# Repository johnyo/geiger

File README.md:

geiger
======

Low Voltage 2.5V PIN Diode Based Geiger Counter

Purpose
======

Super low voltgae Geiger Counter using a modified PIN photodiode. See Bernd Laquai's paper on the subject here: http://www.opengeiger.de/ABGDetektor_en.pdf. The first stage charge amplifier gain is set by the feedback Cap and Resistor. Bigger resistor = more gain, but it pulls the output low and reduces the amplifier's swing on the negative side. 1M is about the biggest resistor you can safely use. The second stage amp takes the negative pulse from the 1st stage and inverts it and boost it x10 so it can be easily read.

Project Structure
=================

/GeigerCounter
* The Eagle PCB project

/Library
* Any components that are not found in the Eagle or SparkFun default libraries, I have made myself and they are here.

/GeigerCounter/FabricationOutput
* This holds the fabrication output script. Based on SparkFun's script. It also holds the zip file Gerber files that were sent out for fabrication.

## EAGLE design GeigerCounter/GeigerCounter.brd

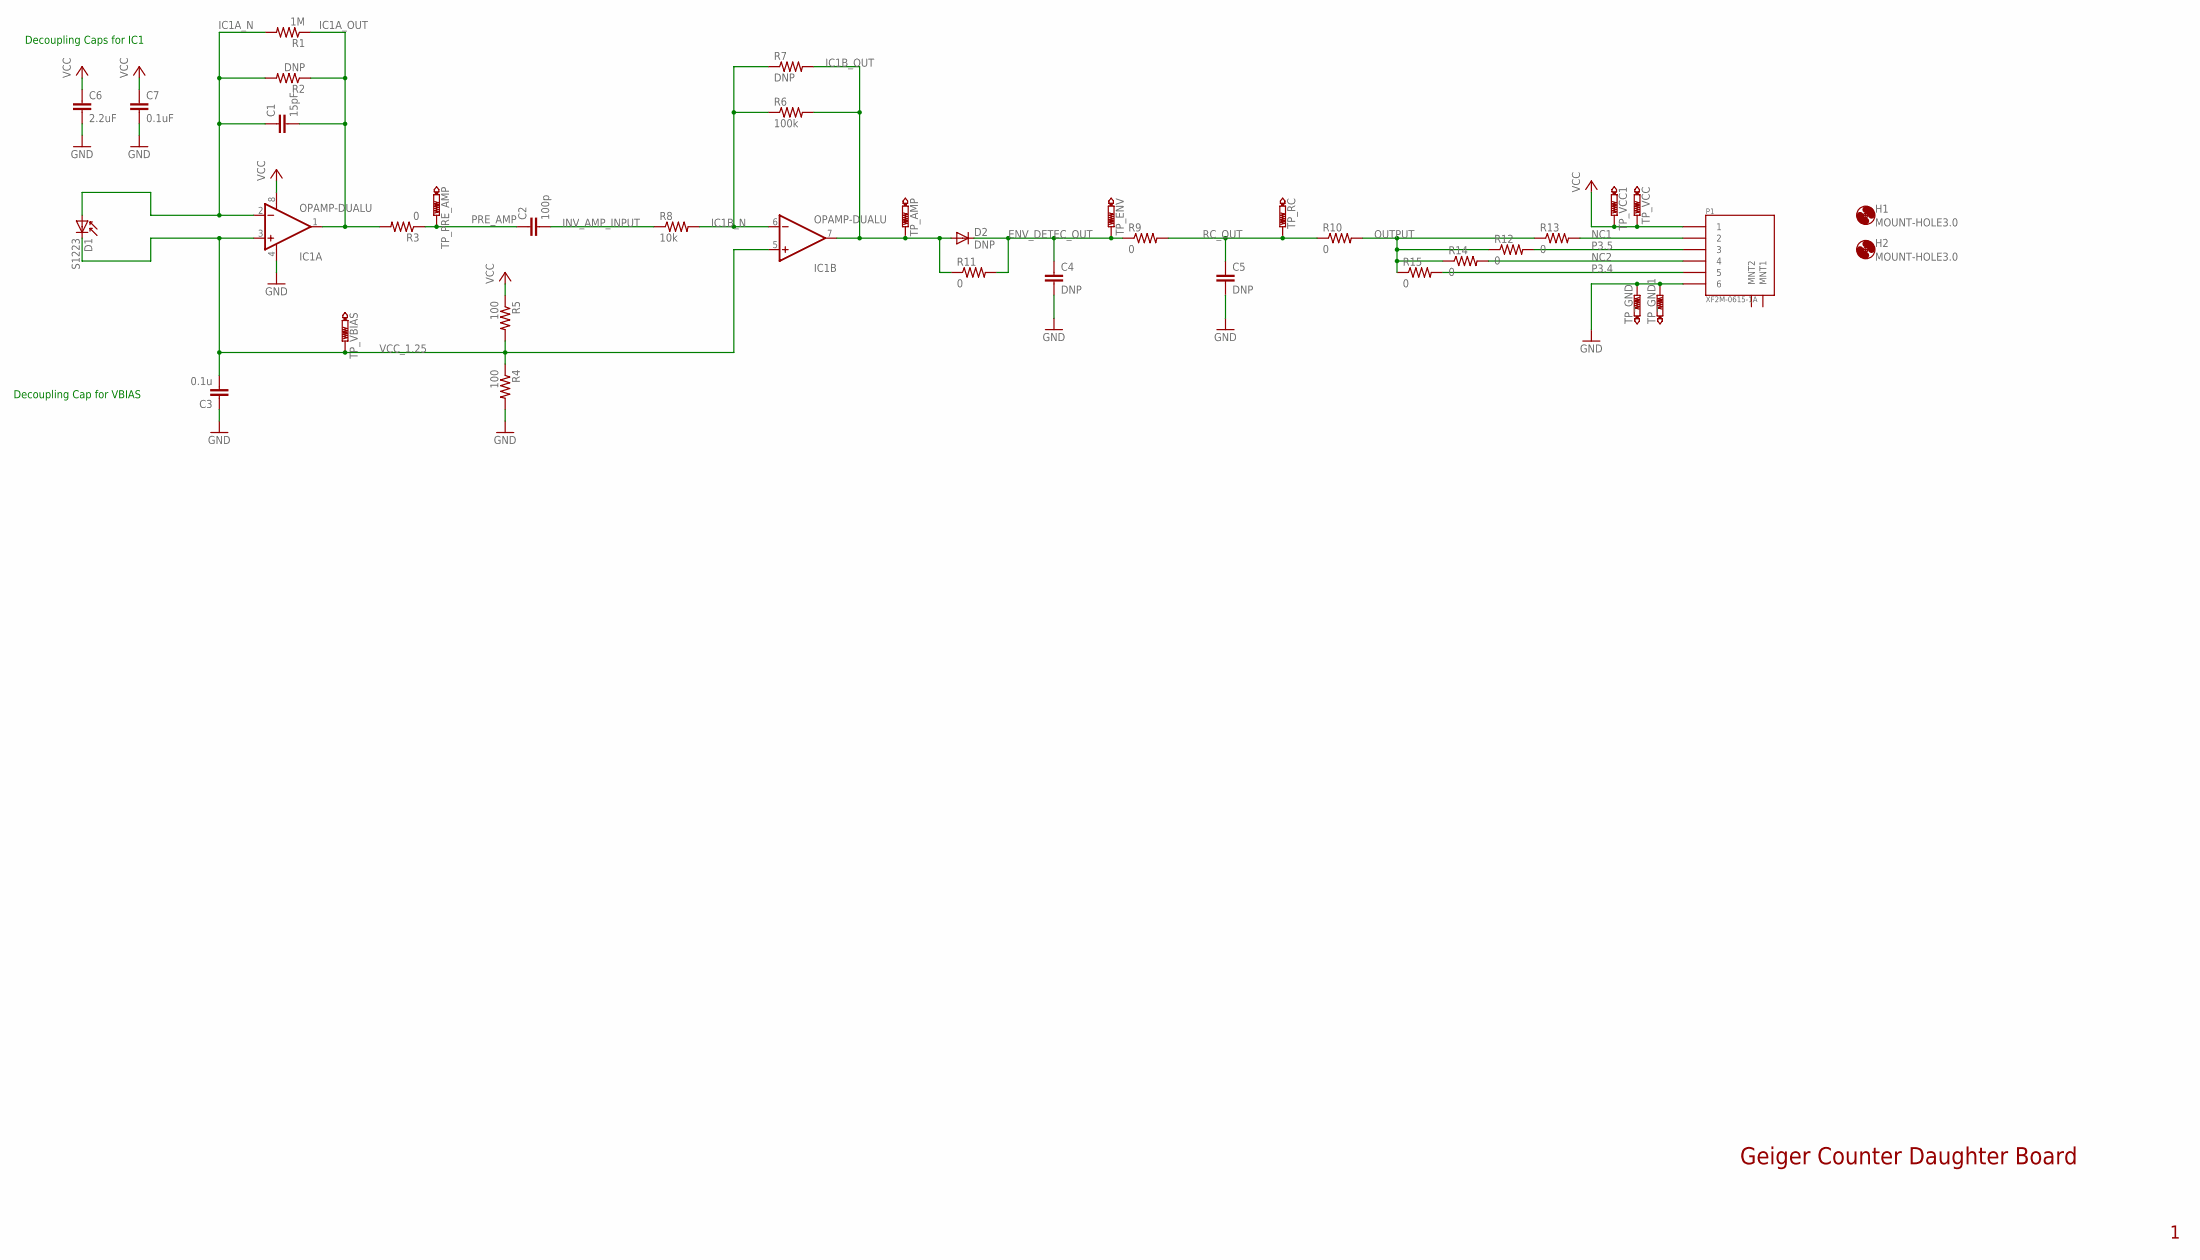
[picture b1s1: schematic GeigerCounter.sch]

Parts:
C1: 15pF; 0603-CAP
C2: 100p; 0603-CAP
C3: 0.1u; 0603-CAP
C4, C5: DNP; 0603-CAP
C6: 2.2uF; 0603-CAP
C7: 0.1uF; 0603-CAP
D1: S1223; DIODE-1N4001
D2: DNP; SOT23-3
H1, H2: MOUNT-HOLE3.0; 3,0
IC1: OPAMP-DUALU; SO08
P1: XF2M-0615-1A
R1: 1M; 0603-RES
R2, R7: DNP; 0603-RES
R3, R9, R10, R11, R12, R13, R14, R15: 0; 0603-RES
R4, R5: 100; 0603-RES
R6: 100k; 0603-RES
R8: 10k; 0603-RES
TP_AMP: PTR1PAD1-20; P1-20
TP_ENV: PTR1PAD1-20; P1-20
TP_GND, TP_GND1: PTR1PAD1-20; P1-20
TP_PRE_AMP: PTR1PAD1-20; P1-20
TP_RC: PTR1PAD1-20; P1-20
TP_VBIAS: PTR1PAD1-20; P1-20
TP_VCC, TP_VCC1: PTR1PAD1-20; P1-20

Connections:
ENV_DETEC_OUT: C4.1, D2.3 (C), R9.1, R11.2, TP_ENV.TP
GND: C3.1, C4.2, C5.2, C6.2, C7.2, IC1.4 (V-), P1.6, R4.2, TP_GND.TP, TP_GND1.TP
IC1A_N: C1.1, D1.A, IC1.2 (-IN), R1.2, R2.2
IC1A_OUT: C1.2, IC1.1 (OUT), R1.1, R2.1, R3.2
IC1B_N: IC1.6 (-IN), R6.1, R7.1, R8.2
IC1B_OUT: D2.1 (A), IC1.7 (OUT), R6.2, R7.2, R11.1, TP_AMP.TP
INV_AMP_INPUT: C2.2, R8.1
NC1: P1.2, R13.2
NC2: P1.4, R14.2
OUTPUT: R10.2, R12.1, R13.1, R14.1, R15.1
P3.4: P1.5, R15.2
P3.5: P1.3, R12.2
PRE_AMP: C2.1, R3.1, TP_PRE_AMP.TP
RC_OUT: C5.1, R9.2, R10.1, TP_RC.TP
VCC: C6.1, C7.1, IC1.8 (V+), P1.1, R5.1, TP_VCC.TP, TP_VCC1.TP
VCC_1.25: C3.2, D1.C, IC1.3 (+IN), IC1.5 (+IN), R4.1, R5.2, TP_VBIAS.TP

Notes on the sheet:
Decoupling Caps for IC1
Decoupling Cap for VBIAS
Geiger Counter Daughter Board

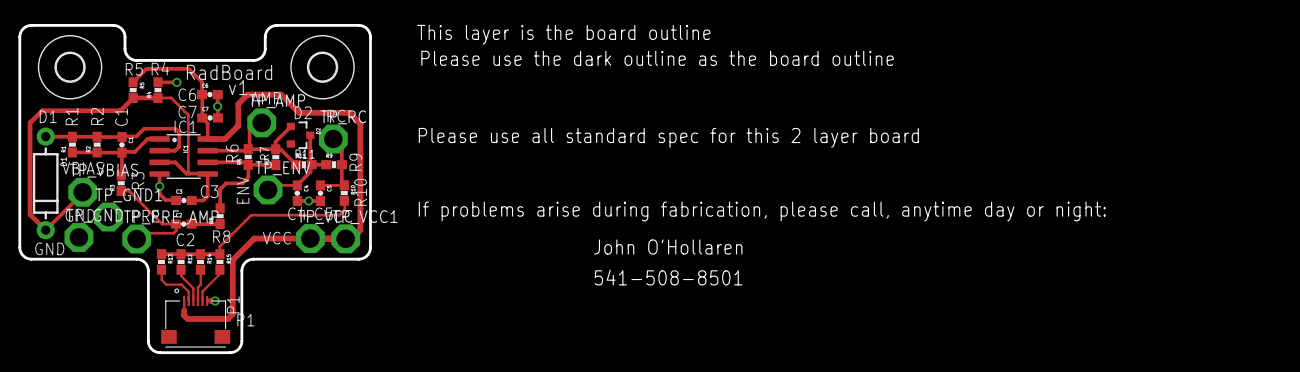
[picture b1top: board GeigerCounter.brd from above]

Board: 2 copper layers, 136.9 x 36.2 mm, 37 parts (0 on the bottom side), 16 nets.

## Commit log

2013-10-19 initial commit, empty project
2013-10-19 Added components and libraries that will be used in the project. I am using a generic op amp footprint, but made a custom photodiode footprint. I am using through hole caps and resistors throughout.
2013-10-19 Added a new library part for the connector I will be using.
2013-10-19 Fixed naming error with connector schematic, it was tValue/tName instead of Value/Name
2013-10-19 preliminary schematic work
2013-10-19 all components placed in schematic
2013-10-23 Added header pins as well as cleaned up schematic a bit. Also added test points
2013-10-23 Added the Bill of Materials
2013-10-23 Updated with new connector on output
2013-10-25 Revised schematic based on working breadboard. Changed footprints to SMD pads.
2013-10-25 Removed BOM
2013-10-25 Layout completed. Routed not yet started.
2013-10-25 Basic routing completed. No pours yet.
2013-10-25 More routing
2013-10-25 Beginning to debug errors. Have not poured ground pour yet.
2013-10-25 All errors from DRC/ERC cleared... need to double check board now
2013-10-25 all errors cleared except Stop Mask errors that I think I will ignore
2013-10-25 Added silkscreen
2013-10-25 All unrouted nets now routed
2013-10-25 Updated OutJob. This is the version that I sent to FreeDRM
2013-11-19 Changed the feedback resistor for the first stage amplifier to be 1M instead of 10M. At 10M it was pulling the output low.

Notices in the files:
parts and their libraries:
SparkFun-AnalogIC: Licensing: CC v3.0 Share-Alike You are welcome to use this library for commercial purposes.
